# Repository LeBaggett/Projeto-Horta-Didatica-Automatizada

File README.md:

# Projeto-Horta-Didatica-Automatizada

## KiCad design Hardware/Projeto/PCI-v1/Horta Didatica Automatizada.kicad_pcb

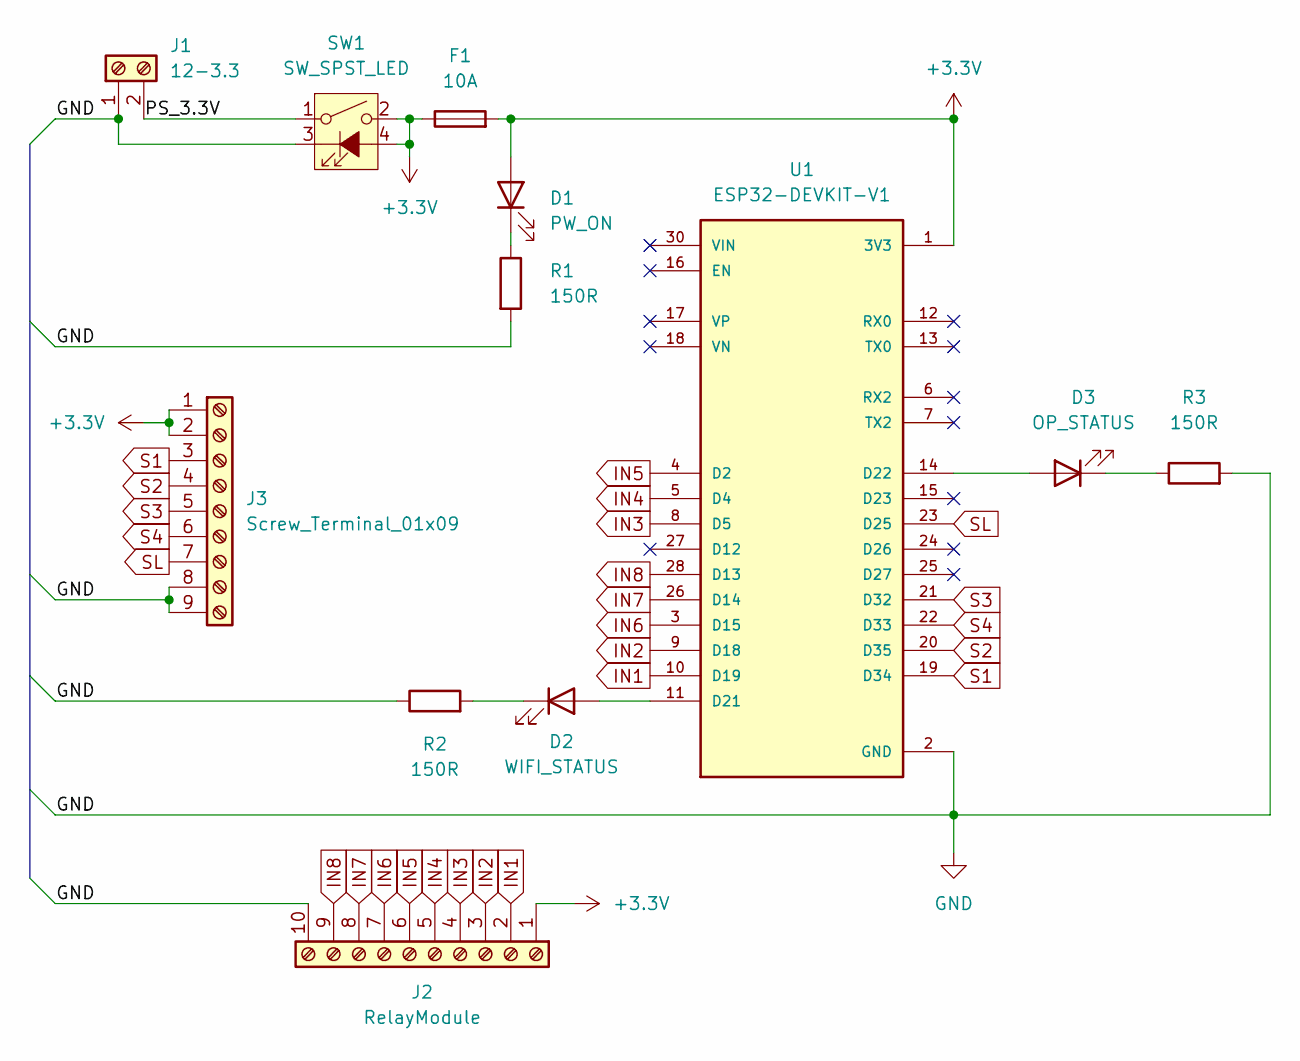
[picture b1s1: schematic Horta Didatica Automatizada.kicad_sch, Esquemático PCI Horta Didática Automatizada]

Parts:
D1: PW_ON; LED_D5.0mm
D2: WIFI_STATUS; LED_D5.0mm_Clear
D3: OP_STATUS; LED_D5.0mm_Clear
F1: 10A; FUSE_4628
J1: 12-3.3; TerminalBlock_Phoenix_MKDS-1,5-2-5.08_1x02_P5.08mm_Horizont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
J2: RelayModule; TerminalBlock_Phoenix_MKDS-1,5-10-5.08_1x10_P5.08mm_Horizon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
J3: Screw_Terminal_01x09; TerminalBlock_Phoenix_MKDS-1,5-9-5.08_1x09_P5.08mm_Horizont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
R1, R2, R3: 150R; R_1206_3216Metric
SW1: SW_SPST_LED; KCD1-106N
U1: ESP32-DEVKIT-V1; MODULE_ESP32_DEVKIT_V1; PARTREV N/A

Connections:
+3.3V: D1.2 (A), F1.1, F1.2, J2.1, J3.1, J3.2, SW1.2, SW1.4 (A), U1.1 (3V3)
/PS_3.3V: J1.2, SW1.1
GND: J1.1, J2.10, J3.8, J3.9, R1.2, R2.1, R3.2, SW1.3 (K), U1.2 (GND), U1.29 (GND)
IN1: J2.2, U1.10 (D19)
IN2: J2.3, U1.9 (D18)
IN3: J2.4, U1.8 (D5)
IN4: J2.5, U1.5 (D4)
IN5: J2.6, U1.4 (D2)
IN6: J2.7, U1.3 (D15)
IN7: J2.8, U1.26 (D14)
IN8: J2.9, U1.28 (D13)
unnamed: D1.1 (K), R1.1
unnamed: D2.2 (A), U1.11 (D21)
unnamed: D2.1 (K), R2.2
unnamed: D3.2 (A), U1.14 (D22)
unnamed: D3.1 (K), R3.1
S1: J3.3, U1.19 (D34)
S2: J3.4, U1.20 (D35)
S3: J3.5, U1.21 (D32)
S4: J3.6, U1.22 (D33)
SL: J3.7, U1.23 (D25)

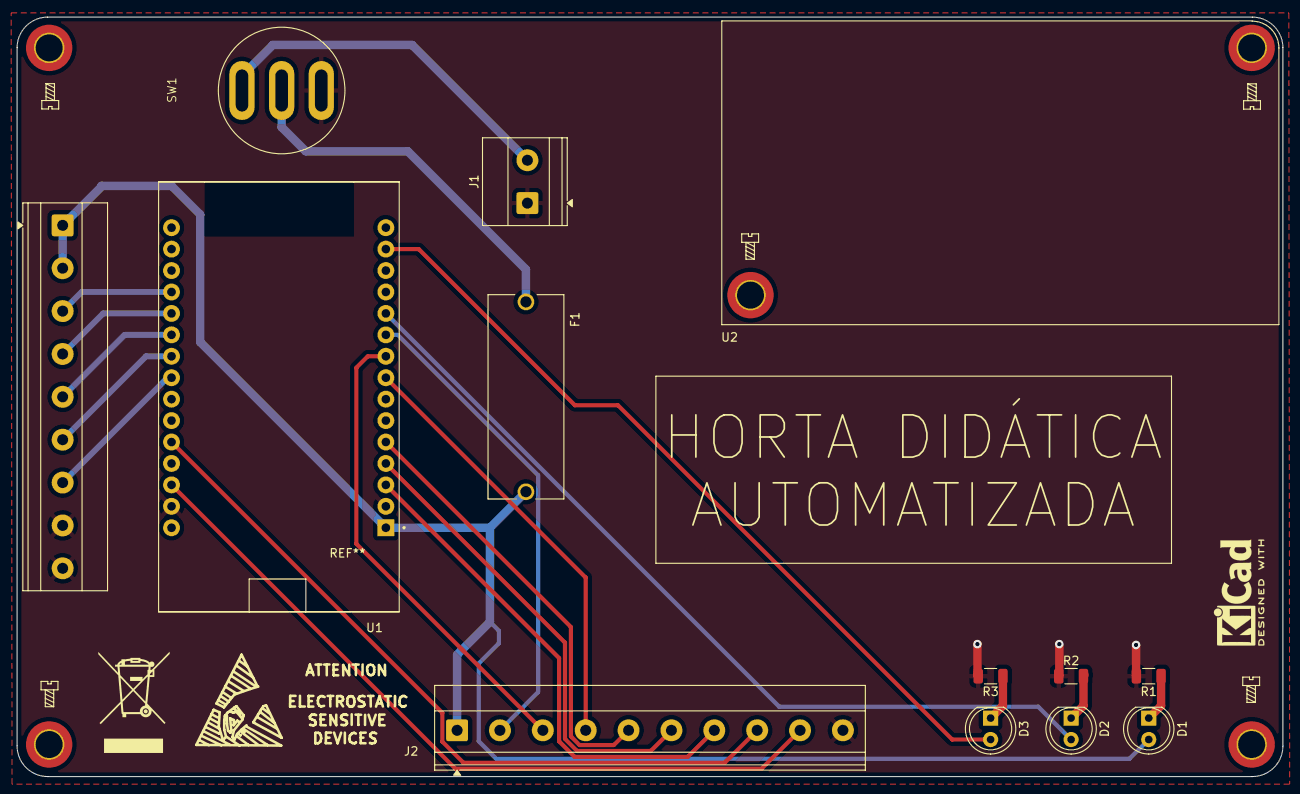
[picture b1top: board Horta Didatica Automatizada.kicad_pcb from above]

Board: 2 copper layers, 150.0 x 90.0 mm, 17 parts (0 on the bottom side), 21 nets.

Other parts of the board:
REF1, REF2, REF3, REF4, REF4#2: MountingHole_3.2mm_M3_ISO14580_Pad_TopOnly

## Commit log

2026-04-13 Fix project title formatting in README
2026-04-13 Fix project title in README
2026-04-17 Reorganização dos ficheiros e adição da versão v1 do projeto
